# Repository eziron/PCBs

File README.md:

# PCB Designs by @eziron1

¡Hola! Soy @eziron1 y en este repositorio encontrarás los diseños y archivos de varias PCBs que he creado. Están disponibles de forma gratuita para que puedas usarlos como base para tus propios proyectos o incluso fabricar mis diseños.

## ¿Qué encontrarás aquí?

- Archivos Gerber de PCBs que he diseñado.
- Archivos de esquemáticos en formato PDF.
- Archivos de diseño en formato EAGLE.

## ¿Cómo usar estos diseños?
Es importante tener en cuenta que mis diseños están hechos de manera específica para mis proyectos. Por lo tanto, al utilizarlos, es posible que necesites realizar ajustes o adaptaciones para tus propias necesidades.

## Proyectos Disponibles

Aquí tienes una lista de los proyectos actualmente en el repositorio. Haz clic en el nombre de cada proyecto para acceder a sus archivos y detalles.

| Proyecto | Descripción Breve |
| :--- | :--- |
| [**Mini Encoder Magnético AS5047P**](./mini%20encoder%20AS5047P) | Mini PCB para el encoder magnético AS5047P, con interfaces SPI y ABI en conectores JST-SH. |
| [**Módulo Inversor con MAX3232**](./inversor) | PCB para la conversión de niveles lógicos RS-232 a TTL, ideal para interfaces seriales. |
| [**SUMO AUTONOMO - Asura Kabuto**](./SUMO_AUTO) | Placa de control principal para un robot de sumo de competición, basada en una Raspberry Pi Pico. |

## Sígueme en Instagram y TikTok

¡Si te gustan mis diseños, sígueme para ver más de mis proyectos y estar al tanto de las novedades!

- [Instagram](https://www.instagram.com/eziron1)
- [TikTok](https://www.tiktok.com/@eziron1)

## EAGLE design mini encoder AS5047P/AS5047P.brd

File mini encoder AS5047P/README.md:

# Mini PCB para Encoder Magnético AS5047P

Diseño de una mini PCB para el encoder magnético de 14 bits **AS5047P**. Esta placa está diseñada para facilitar la integración del sensor en proyectos donde el espacio es limitado, proporcionando un acceso sencillo a sus interfaces SPI y ABI a través de conectores JST-SH.

| Vista Superior de la PCB | Dimensiones |
| :---: | :---: |
|  |  |

## Características Técnicas

- **Encoder Magnético:** AMS AS5047P
- **Tamaño de la PCB:** 17 x 14.8 mm
- **Agujeros de Montaje:** 2x agujeros de Ø2mm, separados por 12mm.
- **Esquinas:** Redondeadas con un radio de ~3.1mm.
- **Conectores:** JST-SH de 1mm pitch SMD (Horizontale/Side).
  - **Puerto SPI:** Conector de 6 pines.
  - **Puerto ABI:** Conector de 5 pines.
- **Selección de Voltaje:** Jumper soldable (SJ1) para elegir entre **3.3V** (puente cerrado) o **5V** (puente abierto).
- **Indicador:** LED de alimentación (D1).

## Lista de Componentes (BOM)

| Referencia | Valor/Componente | Encapsulado |
| :--- | :--- | :--- |
| IC1  | AS5047P       | TSSOP-14     |
| C1, C2 | 0.1uF              | 0402        |
| C3   | 4.7uF              | 0402        |
| D1   | LED Verde/Rojo     | 0402        |
| R1   | 120Ω              | 0402        |
| R2, R3, R4 | 10kΩ               | 0402        |
| JP1  | Conector JST-SH 5P | SM05B-SRSS-TB |
| JP2  | Conector JST-SH 6P | SM06B-SRSS-TB |

## Archivos del Repositorio

- **Archivos de Diseño (Eagle):**
  - `[AS5047P.sch](AS5047P.sch)`: Archivo del esquemático.
  - `[AS5047P.brd](AS5047P.brd)`: Archivo de la placa (board).
- **Archivo de Fabricación:**
  - `[AS5047P_2024-10-15.zip](AS5047P_2024-10-15.zip)`: Paquete con archivos Gerber para fabricación.
- **Documentación y Vistas Previas:**
  - `[AS5047P_esquematico.pdf](AS5047P_esquematico.pdf)`: Esquemático en formato PDF.
  - `[AS5047P_SIZE.pdf](AS5047P_SIZE.pdf)`: Documento PDF con las dimensiones de la PCB.
  - `[CAD.png](CAD.png)`: Imagen del archivo CAD con las geometrías de la PCB.
  - `[AS5047P_TOP.png](AS5047P_TOP.png)`: Imagen de la vista superior de la PCB.
  - `[AS5047P_BUTTON.png](AS5047P_BUTTON.png)`: Imagen de la vista inferior de la PCB.

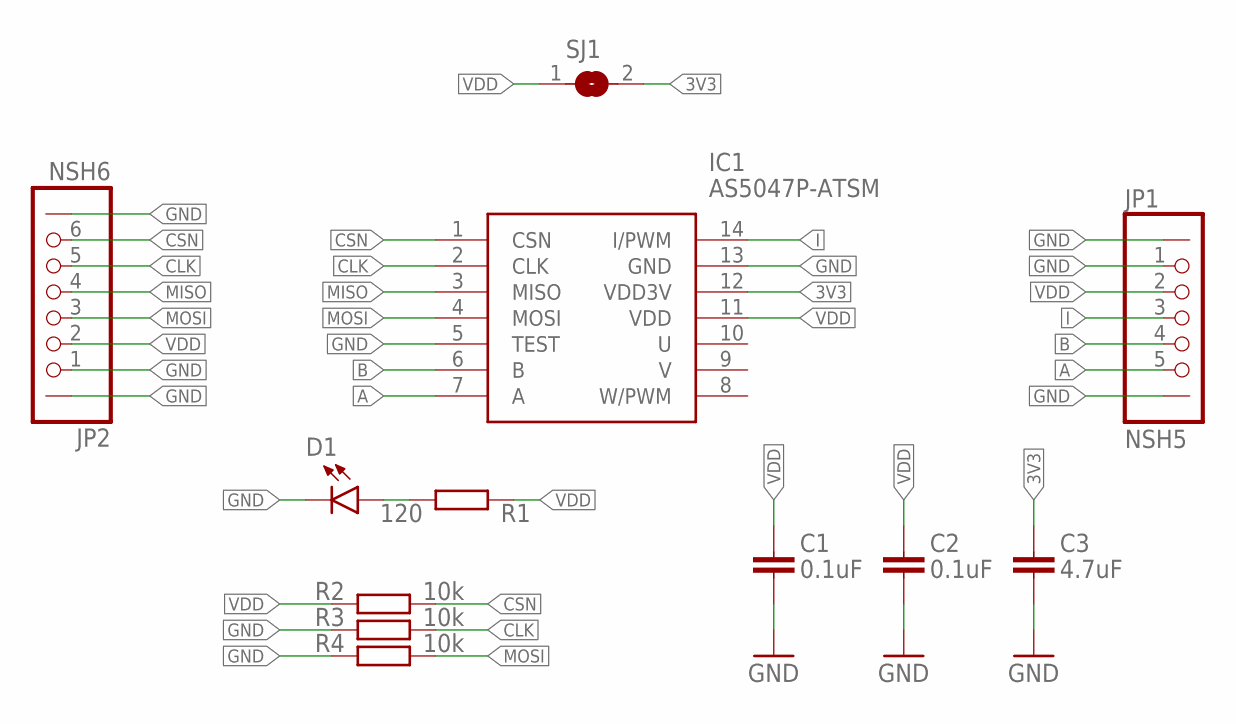
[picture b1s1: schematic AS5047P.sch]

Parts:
C1, C2: 0.1uF; 0402
C3: 4.7uF; 0402
D1: Yellow; LEDC1005X25N_FLAT-B; JLCPCB C72038
IC1: AS5047P-ATSM; SOP65P640X120-14L
JP1: NSH5; NSH_5
JP2: NSH6; NSH_6
R1: 120; 0402
R2, R3, R4: 10k; 0402
SJ1: SJ

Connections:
3V3: C3.1, IC1.12 (VDD3V), SJ1.2
A: IC1.7 (A), JP1.5
B: IC1.6 (B), JP1.4
CLK: IC1.2 (CLK), JP2.5, R3.2
CSN: IC1.1 (CSN), JP2.6, R2.2
GND: C1.2, C2.2, C3.2, D1.C, IC1.5 (TEST), IC1.13 (GND), JP1.1, JP1.P-MOUNT1, JP1.P-MOUNT2, JP2.1, JP2.P-MOUNT1, JP2.P-MOUNT2, R3.1, R4.1
I: IC1.14 (I/PWM), JP1.3
LED_R: D1.A, R1.2
MISO: IC1.3 (MISO), JP2.4
MOSI: IC1.4 (MOSI), JP2.3, R4.2
VDD: C1.1, C2.1, IC1.11 (VDD), JP1.2, JP2.2, R1.1, R2.1, SJ1.1

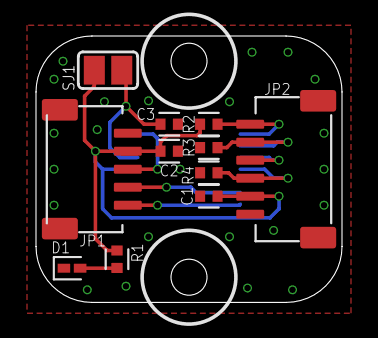
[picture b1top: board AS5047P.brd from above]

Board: 2 copper layers, 17.0 x 14.8 mm, 12 parts (1 on the bottom side), 11 nets.

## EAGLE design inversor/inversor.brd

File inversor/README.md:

# Módulo Inversor con MAX3232

Este repositorio contiene los archivos de diseño de una PCB para un módulo inversor con MAX3232, así como los archivos BOM y CPL necesarios para pedir las PCBs con ensamblaje en JLCPCB.

## Características Técnicas
- **Componente Principal:** MAX3232
- **Capacitores:** 5x SMD 0603 de 0.1uF
- **Resistencias:** 4x SMD 0603 de 330ohm
- **LEDs Indicadores:** 4x SMD 0805
- **Tamaño de la PCB:** 25.4 x 15.24mm (1.0" x 0.6")
- **Separación entre Pines:** 22.86 mm (0.9")

## Archivos Disponibles
- Archivos de diseño de la PCB (Eagle)
- Archivos Gerber para fabricación
- Archivos BOM (Bill of Materials)
- Archivos CPL (Component Placement List)

## Uso
Este módulo está diseñado para proporcionar una interfaz sencilla para los 2 canales del MAX3232. Es ideal para aplicaciones que requieren la conversión de niveles lógicos RS-232 a TTL.

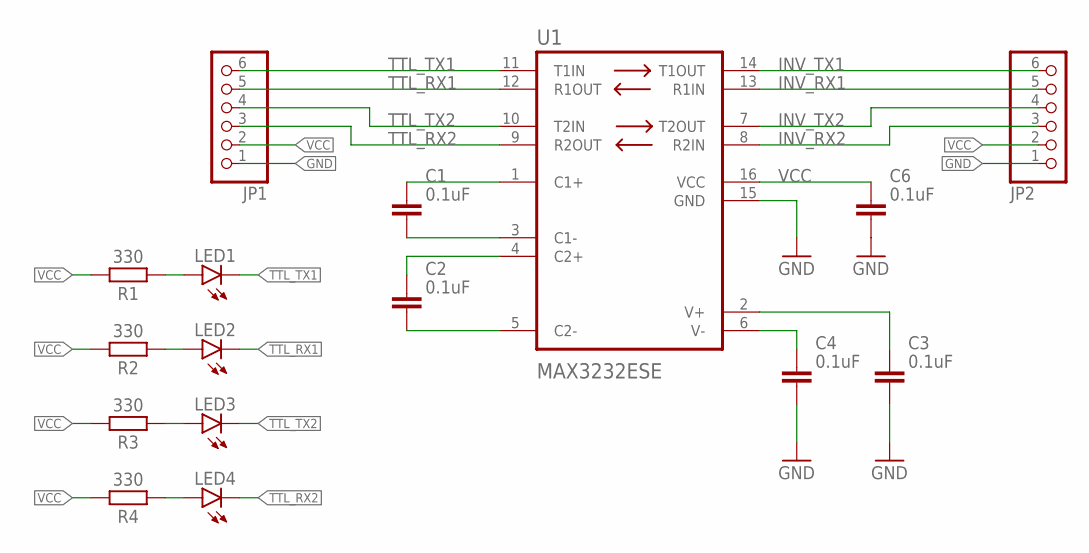
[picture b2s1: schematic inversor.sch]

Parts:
C1, C2, C3, C4, C6: 0.1uF; CAPC1608X85; LCSC C14663
JP1, JP2: PINHD-1X6; 1X06
LED1, LED2, LED3, LED4: LED; CHIPLED_0805; LCSC C2296
R1, R2, R3, R4: 330; RESC1608X60; LCSC C23138
U1: MAX3232ESE; SOIC127P600X175-16N; LCSC C2904738

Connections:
GND: C3.2, C4.2, C6.2, JP1.1, JP2.1, U1.15 (GND)
INV_RX1: JP2.5, U1.13 (R1IN)
INV_RX2: JP2.3, U1.8 (R2IN)
INV_TX1: JP2.6, U1.14 (T1OUT)
INV_TX2: JP2.4, U1.7 (T2OUT)
MAX_C1+: C1.1, U1.1 (C1+)
MAX_C1-: C1.2, U1.3 (C1-)
MAX_C2+: C2.1, U1.4 (C2+)
MAX_C2-: C2.2, U1.5 (C2-)
MAX_V+: C3.1, U1.2 (V+)
MAX_V-: C4.1, U1.6 (V-)
unnamed: LED1.A, R1.1
unnamed: LED2.A, R2.1
unnamed: LED3.A, R3.1
unnamed: LED4.A, R4.1
TTL_RX1: JP1.5, LED2.C, U1.12 (R1OUT)
TTL_RX2: JP1.3, LED4.C, U1.9 (R2OUT)
TTL_TX1: JP1.6, LED1.C, U1.11 (T1IN)
TTL_TX2: JP1.4, LED3.C, U1.10 (T2IN)
VCC: C6.1, JP1.2, JP2.2, R1.2, R2.2, R3.2, R4.2, U1.16 (VCC)

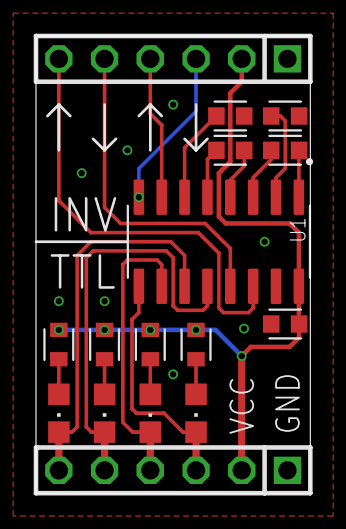
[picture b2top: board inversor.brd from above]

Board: 2 copper layers, 15.2 x 25.4 mm, 16 parts (0 on the bottom side), 20 nets.

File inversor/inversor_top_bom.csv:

Comment,Designator,Footprint,LCSC Part #
0.1uF,C1 C2 C3 C4 C6,CAPC1608X85,C14663
330,R1 R2 R3 R4,RESC1608X60,C23138
LED,LED1 LED2 LED3 LED4,CHIPLED_0805,C19171391
MAX3232ESE,U1,SOIC127P600X175-16N,C15846

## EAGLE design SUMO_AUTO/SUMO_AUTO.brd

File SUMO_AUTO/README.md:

# Asura Kabuto - PCB para Robot Sumo Autónomo

La PCB Asura Kabuto ha sido diseñada para el robot sumo autónomo con el que competí en la ALL JAPAN ROBOT SUMO TOURNAMENT del año 2023. Tiene un tamaño de 100 x 55mm y está basada en una Raspberry Pi Pico, incorporando varios componentes y características específicas para mi robot.

## Características Técnicas
- **Microcontrolador:** Raspberry Pi Pico
- **IMU:** MPU9265
- **Regulador de Voltaje:** MP1584EN a 5V con un diodo SS34
- **Conexión para Odrive 3.6:** Puerto serial y botones de reset para la RPi Pico y Odrive
- **Conexión para Receptor FRsky Archer M+:** Requiere un inversor de señal MAX3232
- **GPIO:** 12 pines para conectar sensores de objetivo, sensores de línea o el MicroStart

## Lista de Componentes (incompleta)
- [Raspberry Pi Pico](https://www.raspberrypi.com/products/raspberry-pi-pico/)
- MPU9265
- MP1584EN a 5V con diodo SS34
- [Odrive 3.6 original](https://odriverobotics.com/shop/odrive-v36) / [Odrive 3.6 Replica](https://es.aliexpress.com/item/1005006314725836.html)
- Receptor FRsky Archer M+
- [Sensor de objetivo JS200XF](https://www.jsumo.com/js200xf-infrared-long-range-sensor)
- [Sensor de linea ML2](https://www.jsumo.com/dual-line-sensor-ml2)
- [Módulo de inicio MicroStart](https://www.jsumo.com/microstart-sumo-minisumo-robot-start-module)

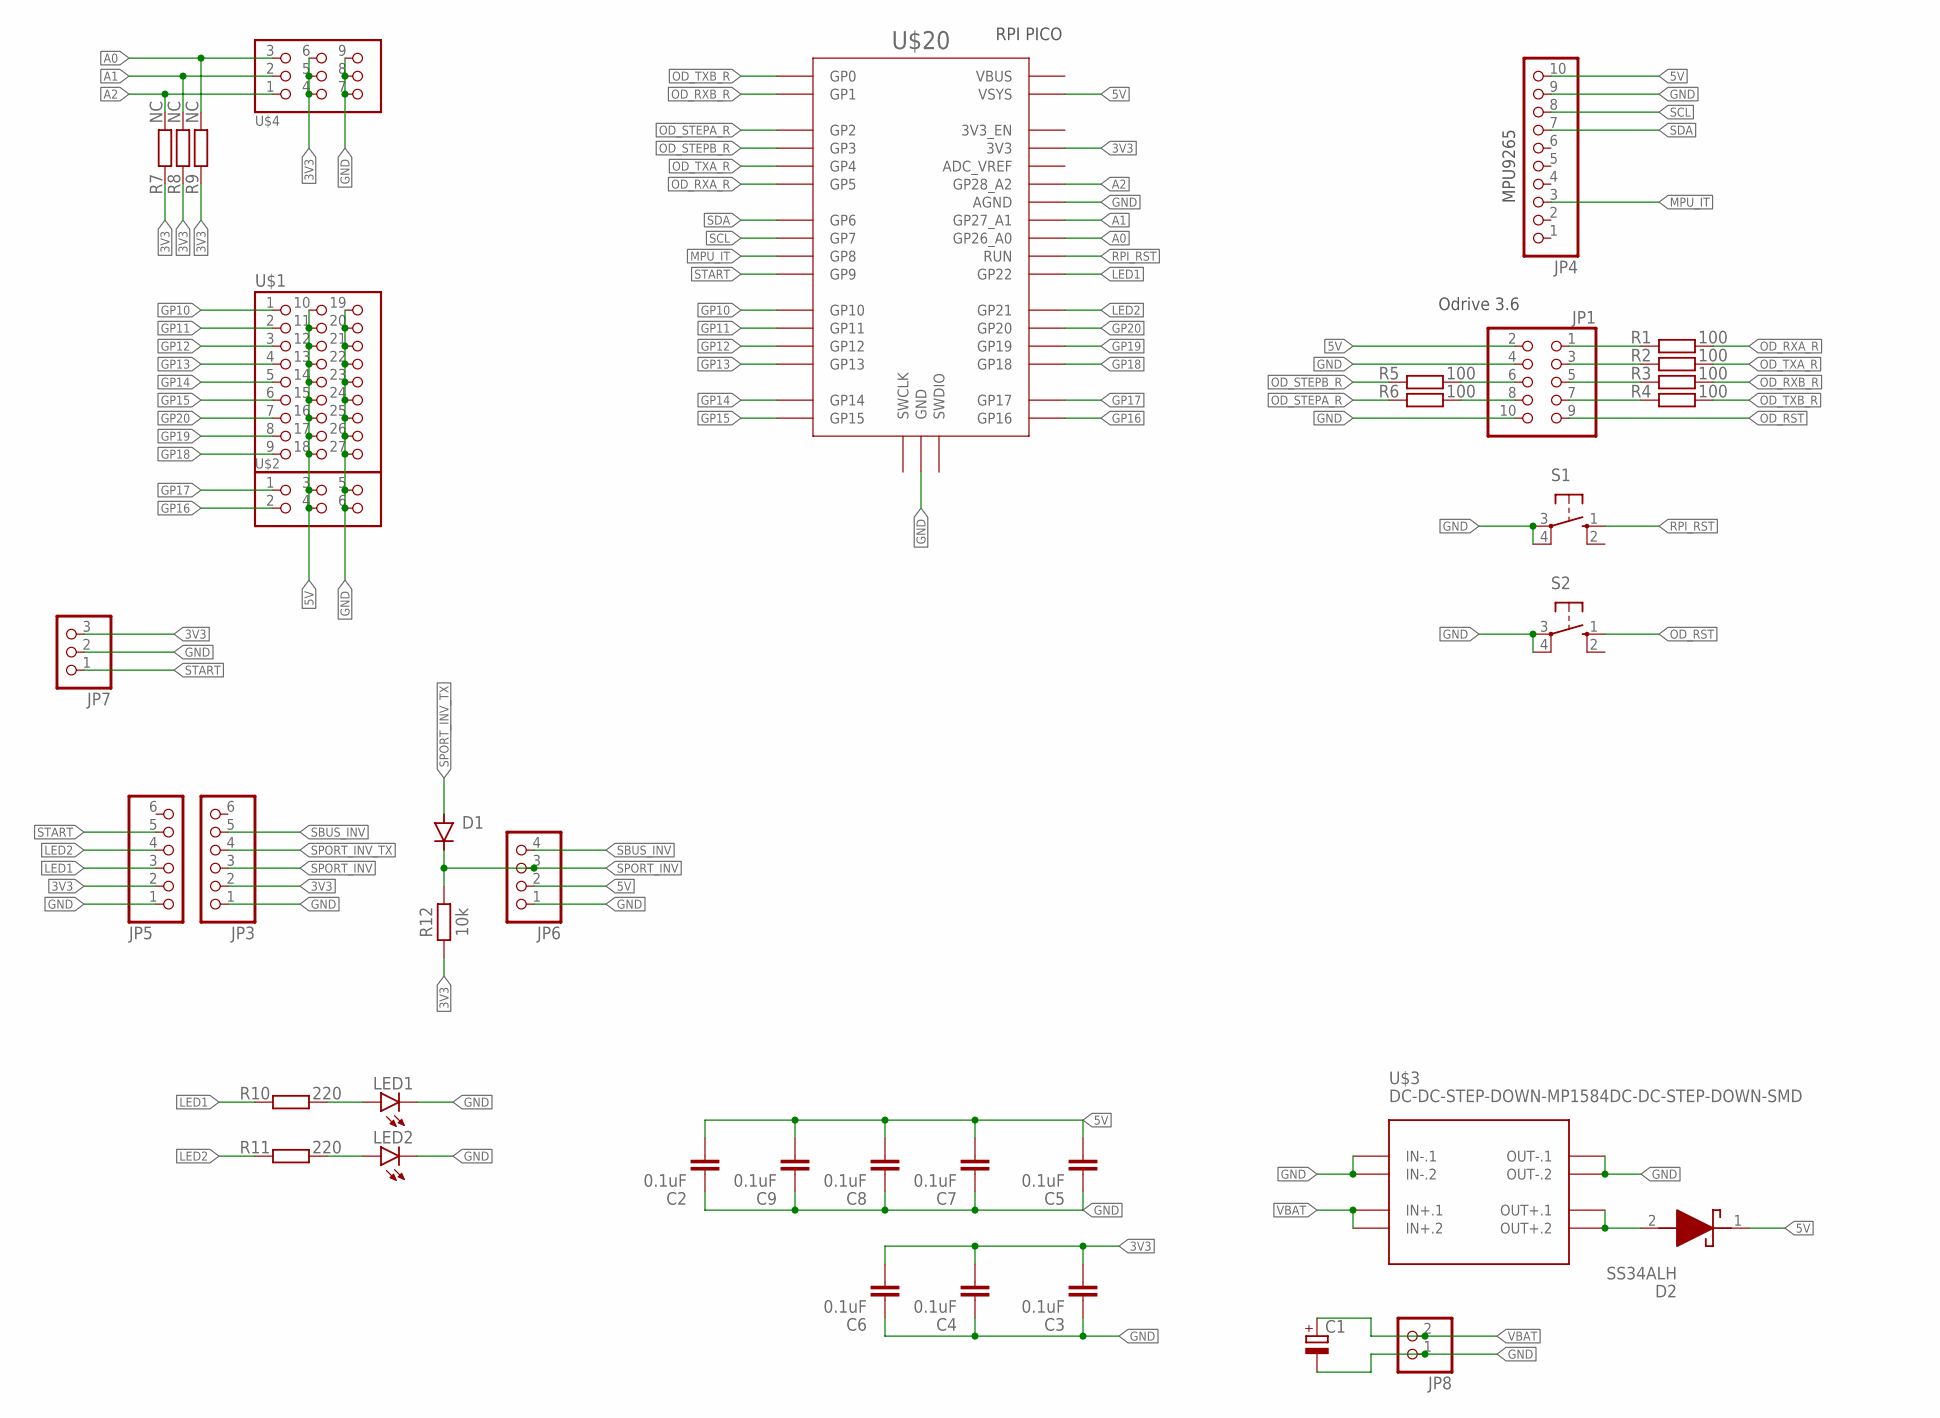
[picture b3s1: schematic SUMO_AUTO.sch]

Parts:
C1: C-POL_TANTALUM-2920(7443-METRIC); CAPMP7443X430N
C2, C3, C4, C5, C6, C7, C8, C9: 0.1uF; 0805; JLCPCB-PART C14663
D1: BAT81; DO34-7
D2: SS34ALH; SODFL5226X100N
JP1: PINHD-2X5; 2X05
JP3, JP5: PINHD-1X6; 1X06
JP4: PINHD-1X10; 1X10
JP6: PINHD-1X4; 1X04
JP7: PINHD-1X3; 1X03
JP8: PINHD-1X2; 1X02
LED1, LED2: LEDCHIP-LED0805; CHIP-LED0805
R1, R2, R3, R4, R5, R6: 100; 0805
R7, R8, R9: NC; 0805
R10, R11: 220; 0805
R12: 10k; 0805
S1, S2: 10-XX; B3F-10XX
U$1: PIN_3X9
U$2: PIN_3X2
U$3: DC-DC-STEP-DOWN-MP1584DC-DC-STEP-DOWN-SMD; DC-DC-STEP-DOWN-SMD
U$4: PIN_3X3
U$20: RPI_PICO-SMD; RPI_PICO

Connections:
3V3: C3.2, C4.2, C6.2, JP3.2, JP5.2, JP7.3, R7.1, R8.1, R9.1, R12.1, U$4.4, U$4.5, U$4.6, U$20.3V3
5V: C2.2, C5.2, C7.2, C8.2, C9.2, D2.1 (K), JP1.2, JP4.10, JP6.2, U$1.10, U$1.11, U$1.12, U$1.13, U$1.14, U$1.15, U$1.16, U$1.17, U$1.18, U$2.3, U$2.4, U$20.VSYS
5V_REG: D2.2 (A), U$3.OUT+.1, U$3.OUT+.2
A0: R9.2, U$4.3, U$20.GP26_A0
A1: R8.2, U$4.2, U$20.GP27_A1
A2: R7.2, U$4.1, U$20.GP28_A2
GND: C1.2 (-), C2.1, C3.1, C4.1, C5.1, C6.1, C7.1, C8.1, C9.1, JP1.4, JP1.10, JP3.1, JP4.9, JP5.1, JP6.1, JP7.2, JP8.1, LED1.C, LED2.C, S1.3, S1.4 (P1), S2.3, S2.4 (P1), U$1.19, U$1.20, U$1.21, U$1.22, U$1.23, U$1.24, U$1.25, U$1.26, U$1.27, U$2.5, U$2.6, U$3.IN-.1, U$3.IN-.2, U$3.OUT-.1, U$3.OUT-.2, U$4.7, U$4.8, U$4.9, U$20.AGND, U$20.GND@1 (GND), U$20.GND@2 (GND), U$20.GND@3 (GND), U$20.GND@4 (GND), U$20.GND@5 (GND), U$20.GND@6 (GND), U$20.GND@7 (GND), U$20.GND@8 (GND)
GP10: U$1.1, U$20.GP10
GP11: U$1.2, U$20.GP11
GP12: U$1.3, U$20.GP12
GP13: U$1.4, U$20.GP13
GP14: U$1.5, U$20.GP14
GP15: U$1.6, U$20.GP15
GP16: U$2.2, U$20.GP16
GP17: U$2.1, U$20.GP17
GP18: U$1.9, U$20.GP18
GP19: U$1.8, U$20.GP19
GP20: U$1.7, U$20.GP20
LED1: JP5.3, R10.1, U$20.GP22
LED1R: LED1.A, R10.2
LED2: JP5.4, R11.1, U$20.GP21
LED2R: LED2.A, R11.2
MPU_IT: JP4.3, U$20.GP8
OD_RST: JP1.9, S2.1 (S)
OD_RXA: JP1.1, R1.1
OD_RXA_R: R1.2, U$20.GP5
OD_RXB: JP1.5, R3.1
OD_RXB_R: R3.2, U$20.GP1
OD_STEPA: JP1.8, R6.2
OD_STEPA_R: R6.1, U$20.GP2
OD_STEPB: JP1.6, R5.2
OD_STEPB_R: R5.1, U$20.GP3
OD_TXA: JP1.3, R2.1
OD_TXA_R: R2.2, U$20.GP4
OD_TXB: JP1.7, R4.1
OD_TXB_R: R4.2, U$20.GP0
RPI_RST: S1.1 (S), U$20.RUN
SBUS_INV: JP3.5, JP6.4
SCL: JP4.8, U$20.GP7
SDA: JP4.7, U$20.GP6
SPORT_INV: D1.C, JP3.3, JP6.3, R12.2
SPORT_INV_TX: D1.A, JP3.4
START: JP5.5, JP7.1, U$20.GP9
VBAT: C1.1 (+), JP8.2, U$3.IN+.1, U$3.IN+.2

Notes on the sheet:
MPU9265
Odrive 3.6
RPI PICO

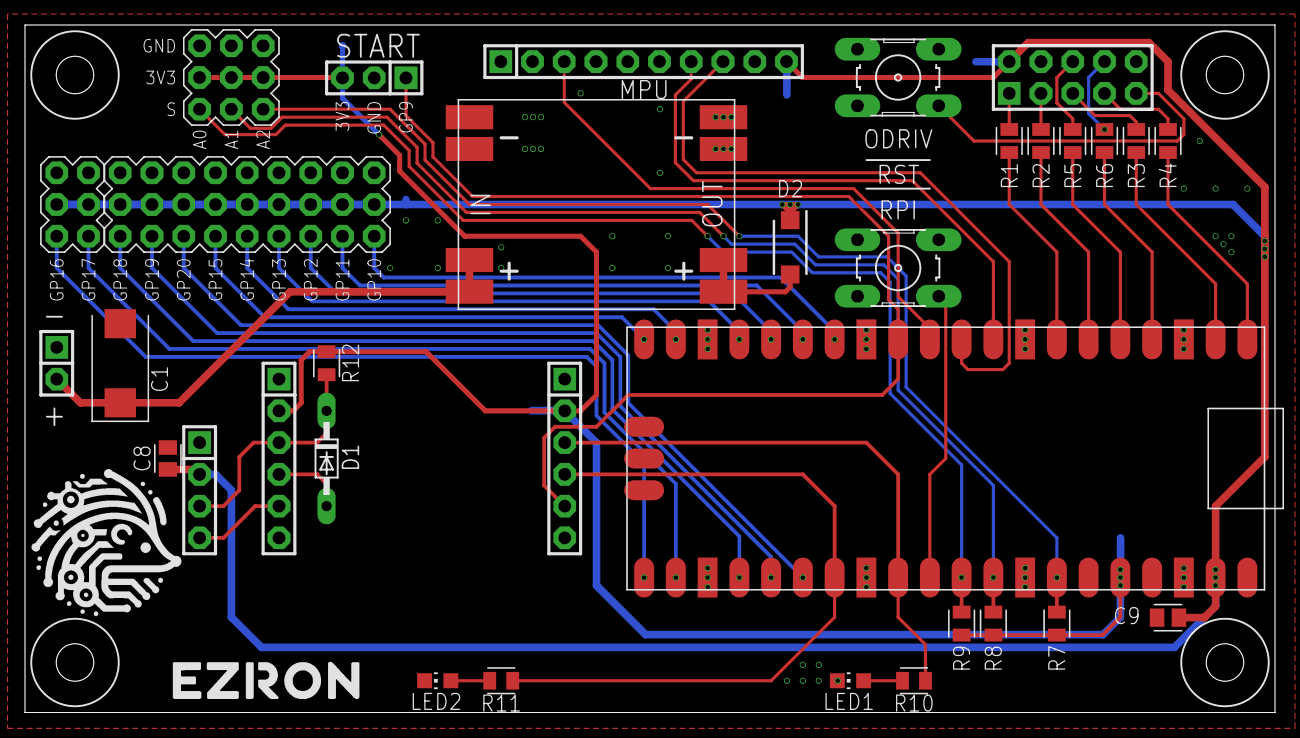
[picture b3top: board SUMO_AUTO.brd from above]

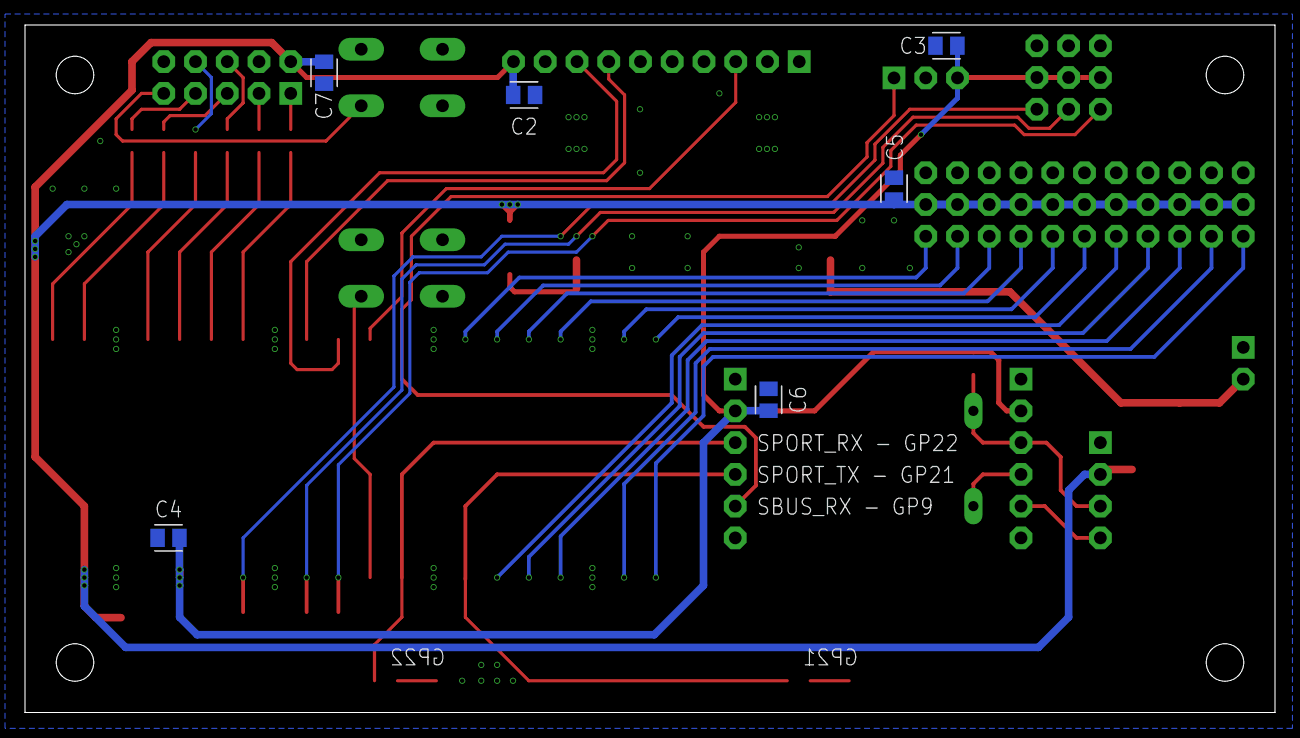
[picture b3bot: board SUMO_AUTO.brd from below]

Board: 2 copper layers, 100.0 x 55.0 mm, 39 parts (6 on the bottom side), 44 nets.

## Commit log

2024-05-09 PCB de mi sumo autónomo con Odrive
2024-05-09 Inversor MAX3232
2024-05-09 inversor
2025-08-05 add AS5047P
